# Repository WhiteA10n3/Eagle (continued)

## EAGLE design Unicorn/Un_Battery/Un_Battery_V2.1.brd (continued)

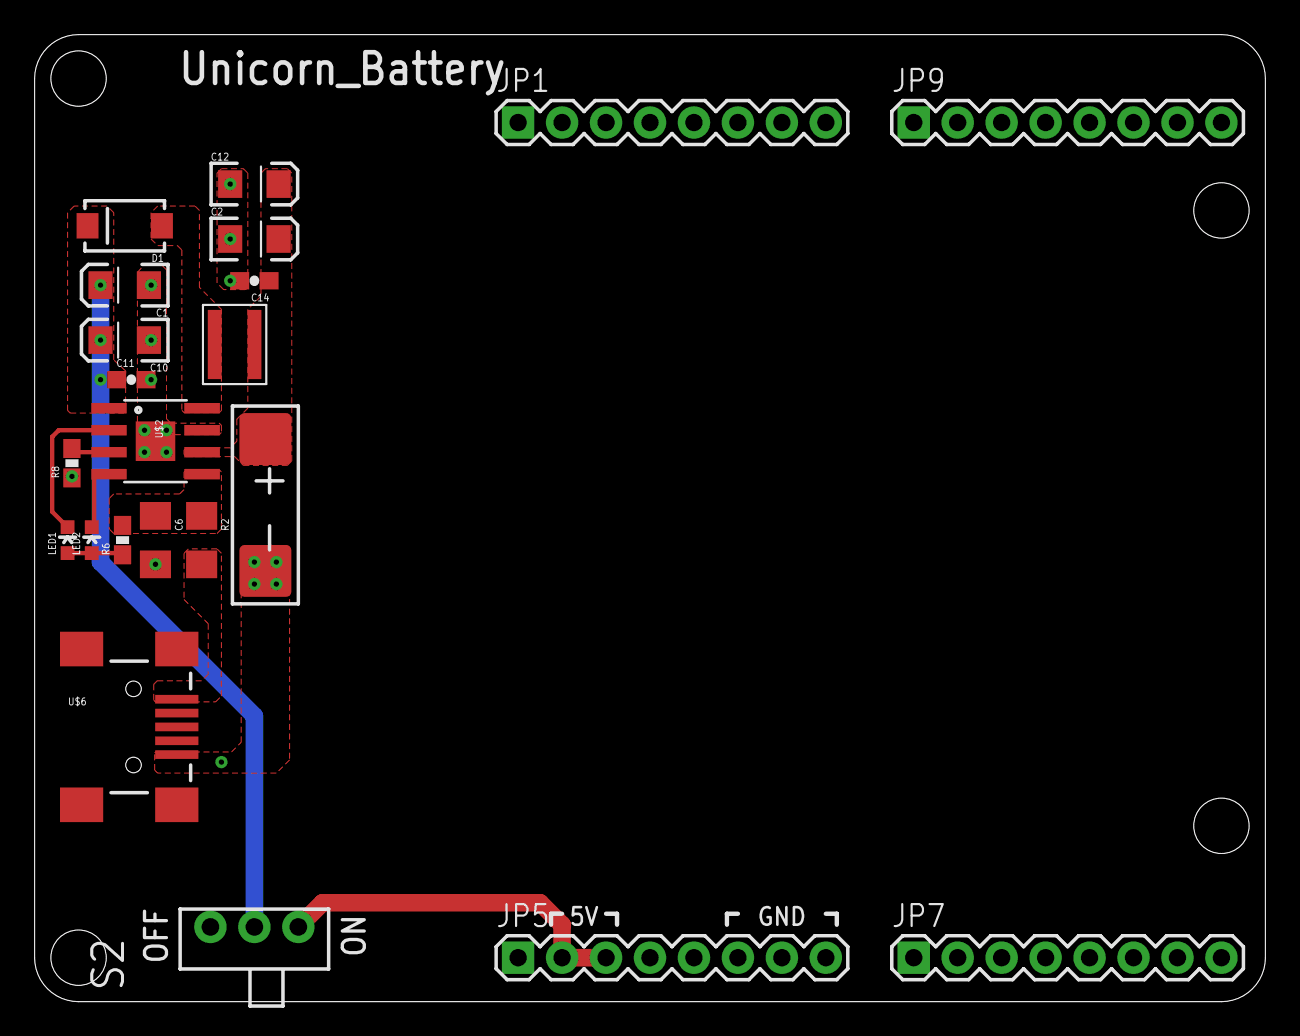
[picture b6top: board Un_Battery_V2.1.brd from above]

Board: 2 copper layers, 71.1 x 55.9 mm, 23 parts (0 on the bottom side), 11 nets.

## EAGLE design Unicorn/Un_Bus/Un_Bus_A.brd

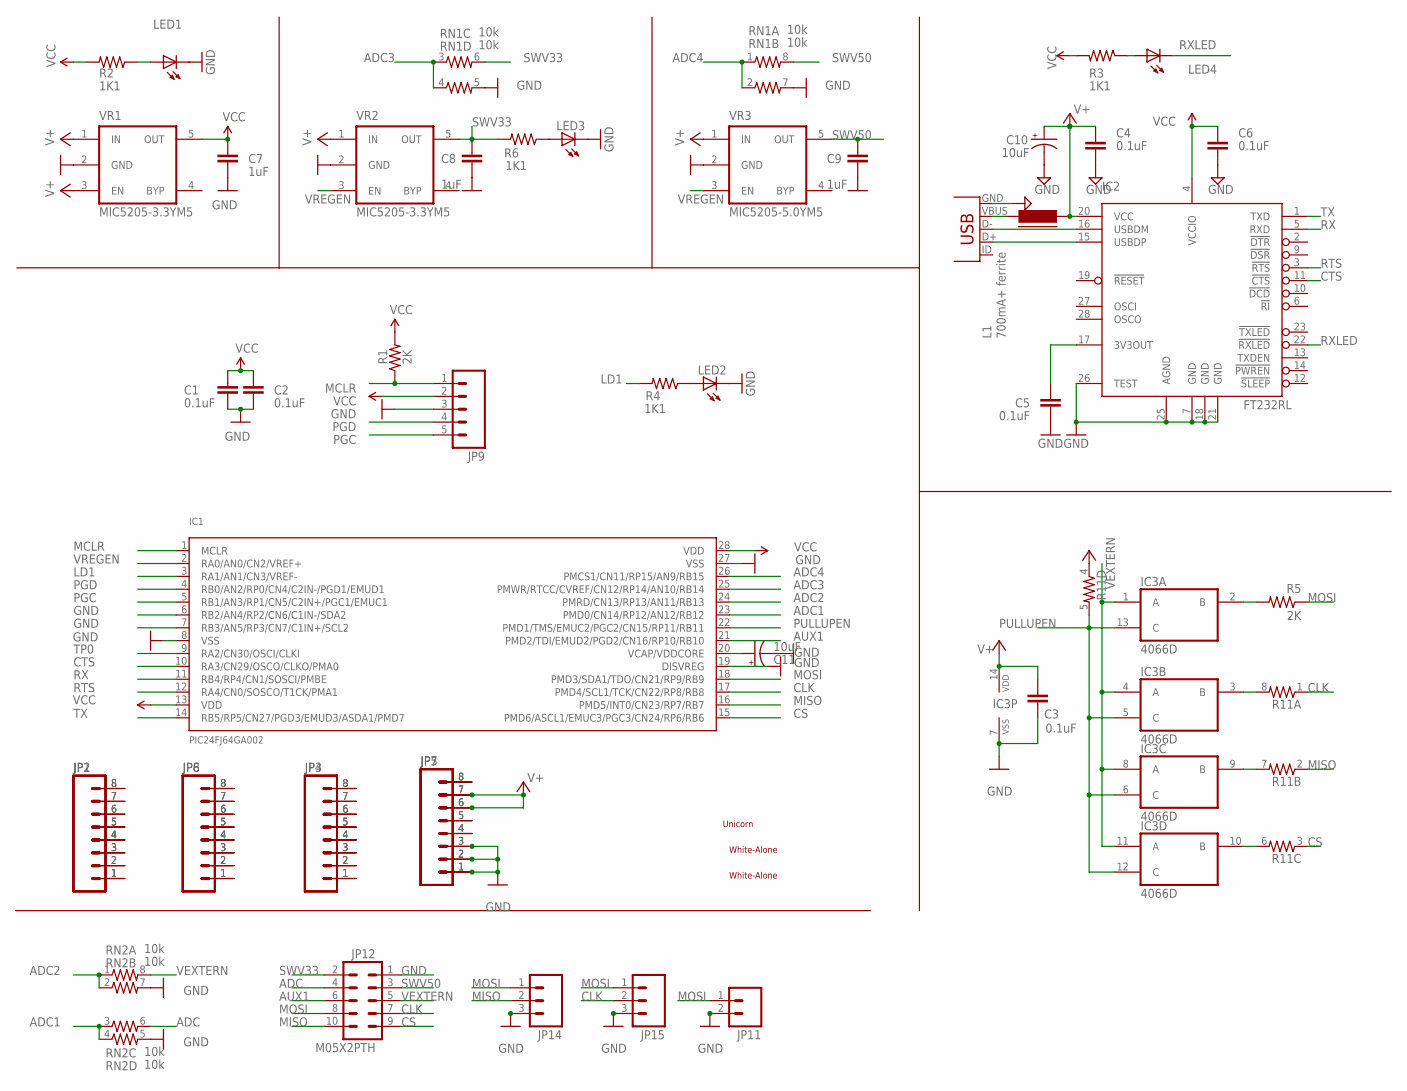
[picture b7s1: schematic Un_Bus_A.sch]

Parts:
C1, C2, C3, C4, C5, C6: 0.1uF; 0603-CAP
C7, C8, C9: 1uF; 0603-CAP
C10, C11: 10uF; EIA3216
IC1: PIC24FJ64GA002; SSOP28
IC2: FT232RL; SSOP28
IC3: 4066D; SO14
JP1, JP2, JP3, JP4, JP5, JP6, JP7, JP8: M081X08; 1X08
JP9: M05PTH; 1X05
JP11: M02PTH; 1X02
JP12: M05X2PTH; AVR_ICSP
JP14, JP15: M03PTH; 1X03
L1: 700mA+ ferrite; FB805
LED1, LED2, LED3, LED4: LED0805; LED-0805
R1, R5: 2K; 0603-RES
R2, R3, R4, R6: 1K1; 0603-RES
R11: RESISTOR-ARRAY; RES-NET-0603
RN1, RN2: 10k; RES-NET-0603
U$1: UNICORN; UNICORN_1
U$2, U$3: WHITE-ALONE_0
VR1, VR2: MIC5205-3.3YM5; SOT-23-5
VR3: MIC5205-5.0YM5; SOT-23-5
X1: USBSMD; USB-MINIB

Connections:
ADC: JP12.4, RN2.6 (2)
ADC1: IC1.23 (PMD0/CN14/RP12/AN12/RB12), RN2.3 (1), RN2.4 (1)
ADC2: IC1.24 (PMRD/CN13/RP13/AN11/RB13), RN2.1, RN2.2 (1)
ADC3: IC1.25 (PMWR/RTCC/CVREF/CN12/RP14/AN10/RB14), RN1.3 (1), RN1.4 (1)
ADC4: IC1.26 (PMCS1/CN11/RP15/AN9/RB15), RN1.1, RN1.2 (1)
AUX1: IC1.21 (PMD2/TDI/EMUD2/PGD2/CN16/RP10/RB10), JP12.6
CLK: IC1.17 (PMD4/SCL1/TCK/CN22/RP8/RB8), JP12.7, JP15.2, R11.1
CS: IC1.15 (PMD6/ASCL1/EMUC3/PGC3/CN24/RP6/RB6), JP12.9, R11.3 (1)
CTS: IC1.10 (RA3/CN29/OSCO/CLKO/PMA0), IC2.11 (!CTS)
GND: C1.2, C2.2, C3.2, C4.2, C5.2, C6.2, C7.2, C8.2, C9.2, C10.C (-), C11.C (-), IC1.6 (RB2/AN4/RP2/CN6/C1IN-/SDA2), IC1.7 (RB3/AN5/RP3/CN7/C1IN+/SCL2), IC1.8 (VSS), IC1.19 (DISVREG), IC1.27 (VSS), IC2.7 (GND), IC2.18 (GND), IC2.21 (GND), IC2.25 (AGND), IC2.26 (TEST), IC3.7 (VSS), JP5.1, JP5.2, JP5.3, JP7.1, JP7.2, JP7.3, JP9.3, JP11.2, JP12.1, JP14.3, JP15.3, LED1.2 (C), LED2.2 (C), LED3.2 (C), RN1.5 (2), RN1.7 (2), RN2.5 (2), RN2.7 (2), VR1.2 (GND), VR2.2 (GND), VR3.2 (GND), X1.GND
LD1: IC1.3 (RA1/AN1/CN3/VREF-), R4.2
MCLR: IC1.1 (MCLR), JP9.1, R1.1
MISO: IC1.16 (PMD5/INT0/CN23/RP7/RB7), JP12.10, JP14.2, R11.2 (1)
MOSI: IC1.18 (PMD3/SDA1/TDO/CN21/RP9/RB9), JP11.1, JP12.8, JP14.1, JP15.1, R5.1
unnamed: IC3.2 (B), R5.2
unnamed: IC3.3 (B), R11.8 (2)
unnamed: C11.A (+), IC1.20 (VCAP/VDDCORE)
unnamed: IC3.10 (B), R11.6 (2)
unnamed: IC3.9 (B), R11.7 (2)
unnamed: LED2.1 (A), R4.1
unnamed: LED1.1 (A), R2.1
unnamed: JP1.1, JP2.1
unnamed: C5.1, IC2.17 (3V3OUT)
unnamed: JP1.2, JP2.2
unnamed: JP1.3, JP2.3
unnamed: JP1.4, JP2.4
unnamed: LED4.1 (A), R3.1
unnamed: JP1.5, JP2.5
unnamed: IC2.15 (USBDP), X1.D+
unnamed: IC2.16 (USBDM), X1.D-
unnamed: JP1.6, JP2.6
unnamed: LED3.1 (A), R6.1
unnamed: JP1.7, JP2.7
unnamed: JP1.8, JP2.8
unnamed: JP3.1, JP4.1
unnamed: JP3.2, JP4.2
unnamed: JP3.3, JP4.3
unnamed: JP3.4, JP4.4
unnamed: JP3.5, JP4.5
unnamed: JP3.6, JP4.6
unnamed: JP3.7, JP4.7
unnamed: JP3.8, JP4.8
unnamed: L1.1, X1.VBUS
unnamed: JP5.4, JP7.4
unnamed: JP6.1, JP8.1
unnamed: JP5.5, JP7.5
unnamed: JP6.2, JP8.2
unnamed: JP6.3, JP8.3
unnamed: JP6.4, JP8.4
unnamed: JP6.5, JP8.5
unnamed: JP6.6, JP8.6
unnamed: JP6.7, JP8.7
unnamed: JP6.8, JP8.8
PGC: IC1.5 (RB1/AN3/RP1/CN5/C2IN+/PGC1/EMUC1), JP9.5
PGD: IC1.4 (RB0/AN2/RP0/CN4/C2IN-/PGD1/EMUD1), JP9.4
PULLUPEN: IC1.22 (PMD1/TMS/EMUC2/PGC2/CN15/RP11/RB11), IC3.5 (C), IC3.6 (C), IC3.12 (C), IC3.13 (C), R11.5 (2)
RST: JP5.8, JP7.8
RTS: IC1.12 (RA4/CN0/SOSCO/T1CK/PMA1), IC2.3 (!RTS)
RX: IC1.11 (RB4/RP4/CN1/SOSCI/PMBE), IC2.5 (RXD)
RXLED: IC2.22 (!RXLED), LED4.2 (C)
SWV33: C8.1, JP12.2, R6.2, RN1.6 (2), VR2.5 (OUT)
SWV50: C9.1, JP12.3, RN1.8 (2), VR3.5 (OUT)
TP0: IC1.9 (RA2/CN30/OSCI/CLKI)
TX: IC1.14 (RB5/RP5/CN27/PGD3/EMUD3/ASDA1/PMD7), IC2.1 (TXD)
V+: C3.1, C4.1, C10.A (+), IC2.20 (VCC), IC3.14 (VDD), JP5.6, JP5.7, JP7.6, JP7.7, L1.2, R11.4 (1), VR1.1 (IN), VR1.3 (EN), VR2.1 (IN), VR3.1 (IN)
VCC: C1.1, C2.1, C6.1, C7.1, IC1.13 (VDD), IC1.28 (VDD), IC2.4 (VCCIO), JP9.2, R1.2, R2.2, R3.2, VR1.5 (OUT)
VEXTERN: IC3.1 (A), IC3.4 (A), IC3.8 (A), IC3.11 (A), JP12.5, RN2.8 (2)
VREGEN: IC1.2 (RA0/AN0/CN2/VREF+), VR2.3 (EN), VR3.3 (EN)

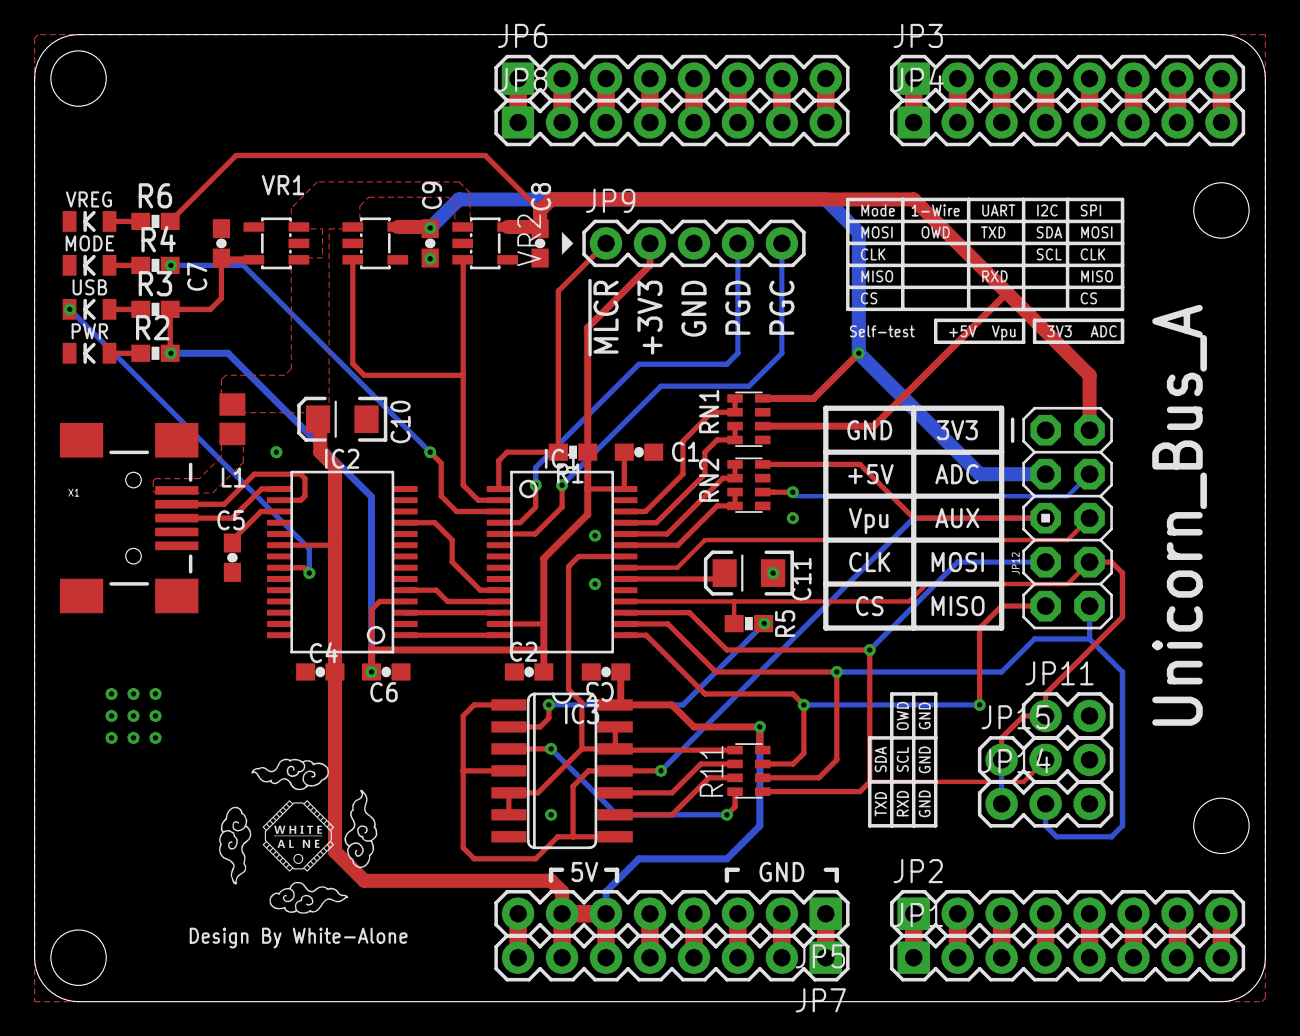
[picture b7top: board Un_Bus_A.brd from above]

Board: 2 copper layers, 71.1 x 55.9 mm, 48 parts (1 on the bottom side), 67 nets.
